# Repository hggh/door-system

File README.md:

# door-system

## parts
 * push button
 * reed contact
 * 2x WS2812 strip
   * outdoor 52 LEDs
   * indoor 52 LEDs
 * LD33V (5V to 3.3V)
 * ESP12E

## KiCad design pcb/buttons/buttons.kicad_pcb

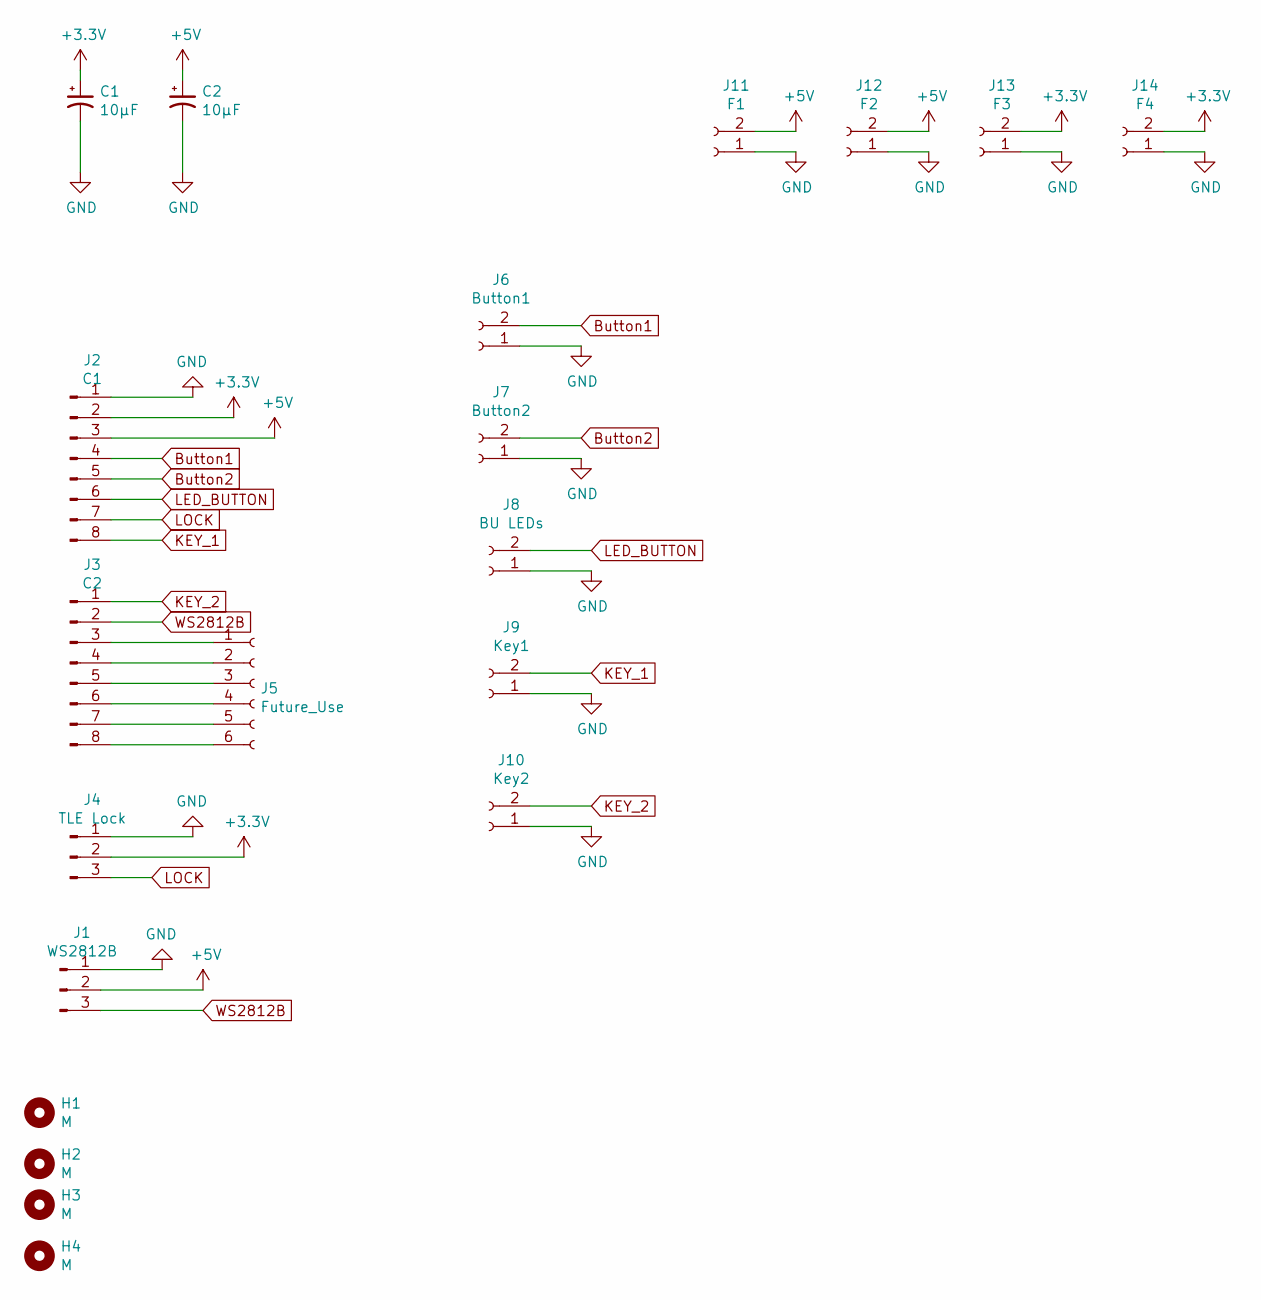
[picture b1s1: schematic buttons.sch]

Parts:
C1: 10µF; CP_Radial_D5.0mm_P2.00mm
C2: 10µF; CP_Radial_D5.0mm_P2.50mm
H1, H2, H3, H4: M; MountingHole_3.2mm_M3
J1: WS2812B; PinHeader_1x03_P2.54mm_Horizontal
J2: C1; PinHeader_1x08_P2.54mm_Horizontal
J3: C2; PinHeader_1x08_P2.54mm_Horizontal
J4: TLE Lock; PinHeader_1x03_P2.54mm_Horizontal
J5: Future_Use; PinHeader_1x06_P2.54mm_Vertical
J6: Button1; PinHeader_1x02_P2.54mm_Vertical
J7: Button2; PinHeader_1x02_P2.54mm_Vertical
J8: BU LEDs; PinHeader_1x02_P2.54mm_Vertical
J9: Key1; PinHeader_1x02_P2.54mm_Vertical
J10: Key2; PinHeader_1x02_P2.54mm_Vertical
J11: F1; PinHeader_1x02_P2.54mm_Vertical
J12: F2; PinHeader_1x02_P2.54mm_Vertical
J13: F3; PinHeader_1x02_P2.54mm_Vertical
J14: F4; PinHeader_1x02_P2.54mm_Vertical

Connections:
+3V3: C1.1, J2.2, J4.2, J13.2, J14.2
+5V: C2.1, J1.2, J2.3, J11.2, J12.2
Button1: J2.4, J6.2
Button2: J2.5, J7.2
GND: C1.2, C2.2, J1.1, J2.1, J4.1, J6.1, J7.1, J8.1, J9.1, J10.1, J11.1, J12.1, J13.1, J14.1
KEY_1: J2.8, J9.2
KEY_2: J3.1, J10.2
LED_BUTTON: J2.6, J8.2
LOCK: J2.7, J4.3
unnamed: J3.3, J5.1
unnamed: J3.4, J5.2
unnamed: J3.5, J5.3
unnamed: J3.6, J5.4
unnamed: J3.7, J5.5
unnamed: J3.8, J5.6
WS2812B: J1.3, J3.2

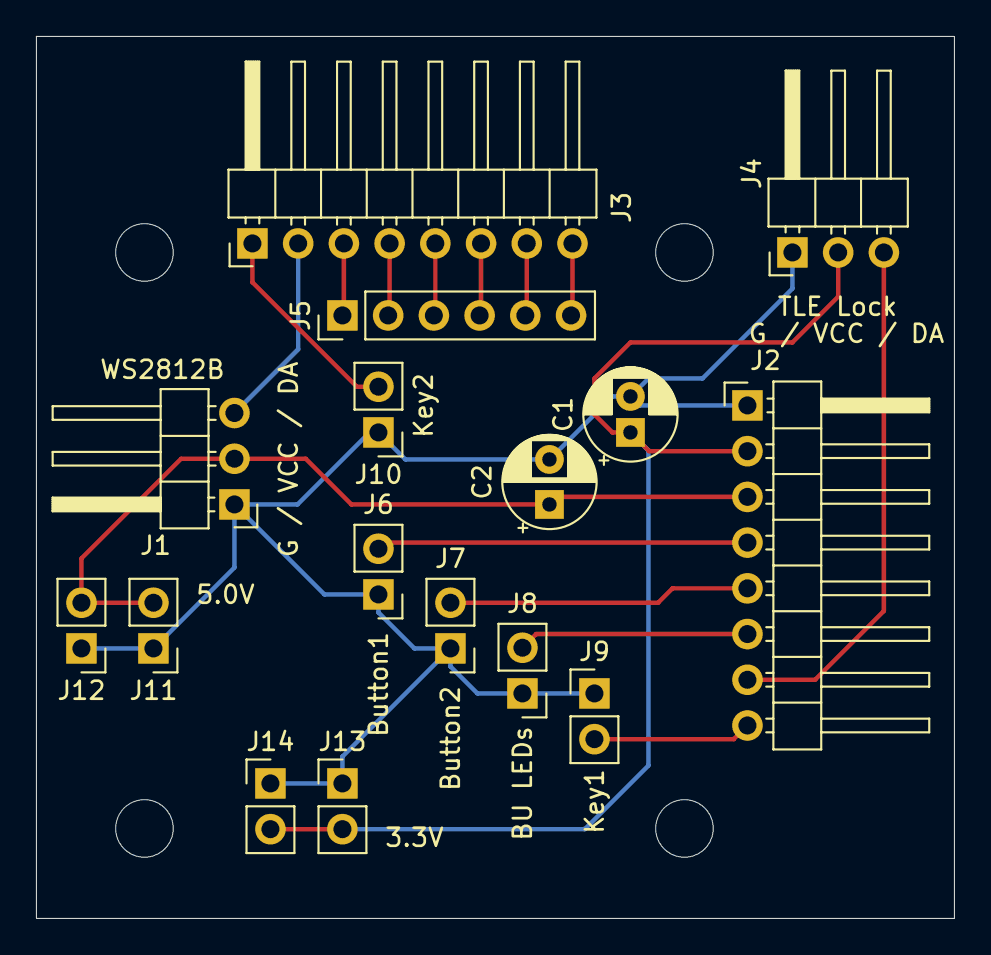
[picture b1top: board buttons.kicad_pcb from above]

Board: 2 copper layers, 51.0 x 49.0 mm, 20 parts (0 on the bottom side), 16 nets.

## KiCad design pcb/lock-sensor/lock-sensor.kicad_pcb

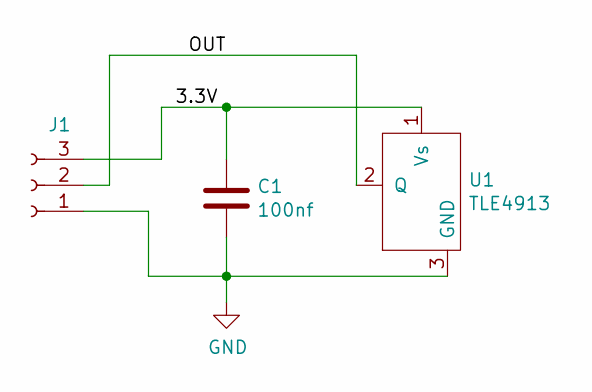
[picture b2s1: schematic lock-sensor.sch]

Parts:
C1: 100nf; C_0805_2012Metric
J1: Conn_01x03_Female; PinHeader_1x03_P2.00mm_Vertical
U1: TLE4913; SC-59

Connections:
/3.3V: C1.1, J1.3, U1.1 (Vs)
/OUT: J1.2, U1.2 (Q)
GND: C1.2, J1.1, U1.3 (GND)

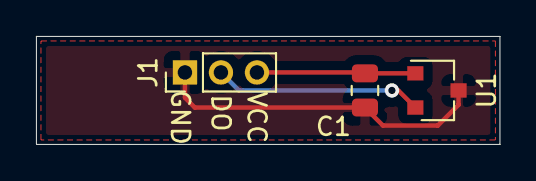
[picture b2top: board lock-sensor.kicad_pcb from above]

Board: 2 copper layers, 25.8 x 6.0 mm, 3 parts (0 on the bottom side), 3 nets.

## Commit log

2017-10-08 initial
2017-10-08 fix isr
2017-11-16 initial layout
2018-03-21 Updated Door Status
2018-04-09 move FastLED.show into main loop
2018-04-30 add hardware button to switch off all lights
2018-09-21 changed to platformIO
2018-11-24 added brightness
2018-11-24 added case for Step Motor
2018-11-29 added ready stl
2018-12-02 bigger middle hole
2019-03-02 added wood light pipe holder
2019-03-11 updated svg
2019-03-11 rework to esp8266 12e mqtt sending door status
2019-10-04 two led strips; add button, mqtt subscribe
2019-10-05 update code
2019-10-05 update interval ; fix queue name
2019-10-19 change to neopixel and add mqtt connection check
2019-11-08 set dhcp hostname
2020-12-19 pio update
2020-12-29 add lock sensor pcb
2020-12-29 never used
2020-12-31 esp32 update with test cases
2021-01-21 add pcb for buttons
2021-01-25 final pcb
2021-06-24 update pins
2021-06-24 cases
2023-03-30 add keyholder 1
